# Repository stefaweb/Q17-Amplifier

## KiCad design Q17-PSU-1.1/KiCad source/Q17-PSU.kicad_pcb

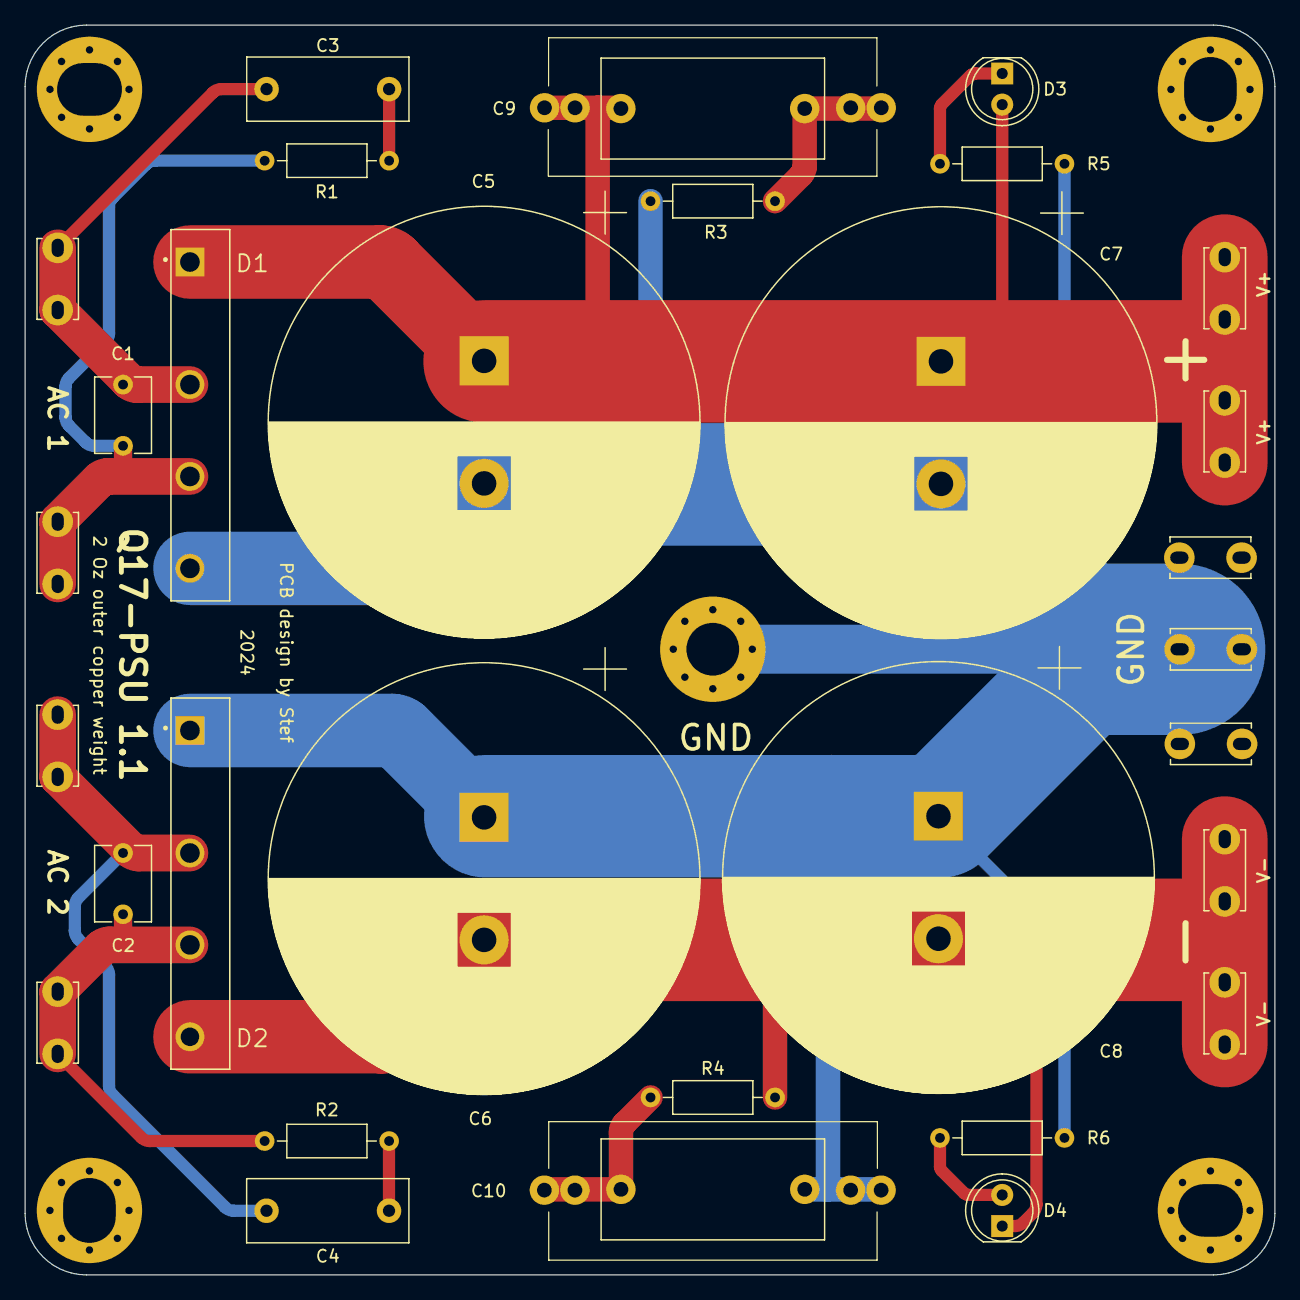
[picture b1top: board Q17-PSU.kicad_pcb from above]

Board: 2 copper layers, 102.0 x 102.0 mm, 31 parts (0 on the bottom side), 13 nets.

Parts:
C1, C2: 10nF; C_Disc_D6.0mm_W4.4mm_P5.00mm
C3, C4: 10nF; C_Rect_L13.0mm_W5.0mm_P10.00mm_FKS3_FKP3_MKS4
C5, C6, C7, C8: 10000uF 63v; CP_Radial_D35.0mm_P10.00mm_SnapIn
C9: 220nf; C_Rect_Q17_PSU_L26.50_H11.00_P20.50
C10: 220nF; C_Rect_Q17_PSU_L26.50_H11.00_P20.50
D1, D2: GBJ2510; DIOB_GBJ2510
D3, D4: LED; LED_D5.0mm
J1-1: AC1-1; Faston_Connector_63849-1_TEC
J1-2: AC1-2; Faston_Connector_63849-1_TEC
J1-3: AC2-1; Faston_Connector_63849-1_TEC
J1-4: AC2-2; Faston_Connector_63849-1_TEC
J2-1, J2-2: V+; Faston_Connector_63849-1_TEC
J2-3, J2-4, J2-5: GNDPWR; Faston_Connector_63849-1_TEC
J2-6, J2-7: V-; Faston_Connector_63849-1_TEC
R1, R2, R3, R4: 10R; R_Axial_DIN0207_L6.3mm_D2.5mm_P10.16mm_Horizontal
R5, R6: 10K; R_Axial_DIN0207_L6.3mm_D2.5mm_P10.16mm_Horizontal

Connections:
GNDPWR: C5.2, C6.1, C7.2, C8.1, C10.1, D1.4, D2.1, J2-3.1, J2-4.1, J2-5.1, R3.2, R5.2, R6.1
unnamed: C3.2, R1.1
unnamed: C4.2, R2.1
unnamed: C9.2, R3.1
unnamed: C10.2, R4.1
unnamed: C5.1, C7.1, C9.1, D1.1, D3.2 (A), J2-1.1, J2-2.1
unnamed: D3.1 (K), R5.1
unnamed: D4.2 (A), R6.2
unnamed: C6.2, C8.2, D2.4, D4.1 (K), J2-6.1, J2-7.1, R4.2
unnamed: C1.1, C3.1, D1.2, J1-1.1
unnamed: C1.2, D1.3, J1-2.1, R1.2
unnamed: C2.1, C4.1, D2.2, J1-3.1
unnamed: C2.2, D2.3, J1-4.1, R2.2

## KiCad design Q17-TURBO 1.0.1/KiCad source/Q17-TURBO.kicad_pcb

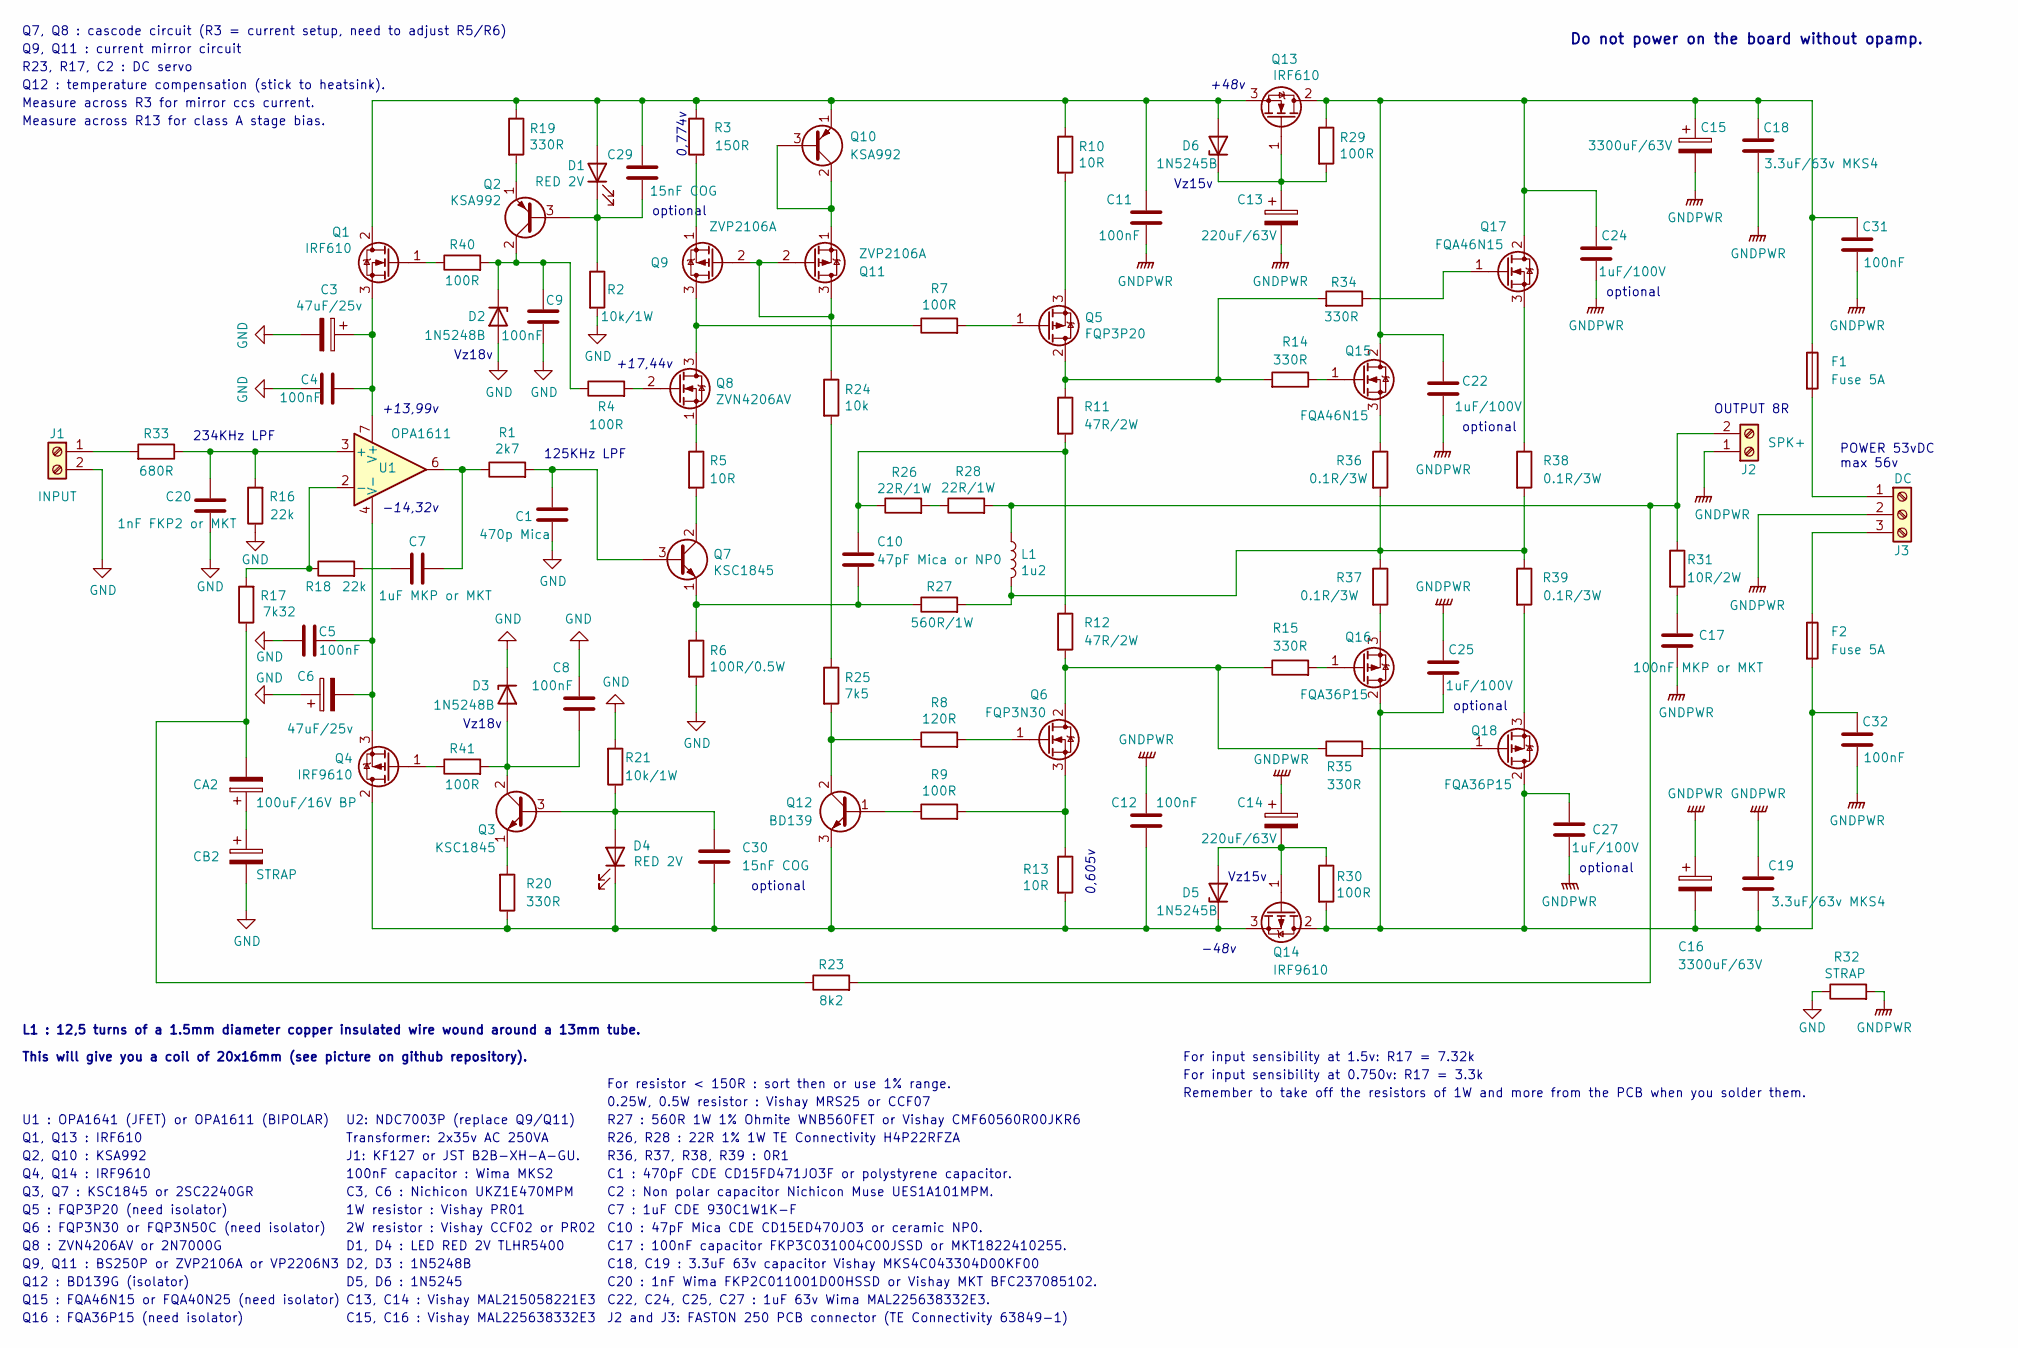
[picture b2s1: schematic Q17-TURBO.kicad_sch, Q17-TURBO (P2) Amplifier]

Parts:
C1: 470p Mica; C_Mica_v2_L11.4mm_W4.3mm_H9.1_P5.9mm_mix; Part# CD15FD471JO3F
C3, C6: 47uF/25v; CP_Radial_D10.0mm_P5.00mm; Part# Nichicon Muse UKZ1E470MPM
C4, C5, C8, C9, C11, C12, C31, C32: 100nF; C_Rect_L7.2mm_W2.5mm_P5.00mm_FKS2_FKP2_MKS2_MKP2; Part# MKS2D031001A00KSSD
C7: 1uF MKP or MKT; C_Rect_C7_Q17_Mini_L26.50_H11.00_P20.50_2; Part# CDE 930C1W1K-F
C10: 47pF Mica or NP0; C_Mica_v2_L11.4mm_W4.3mm_H9.1_P5.9mm_mix; Part# CD15ED470JO3
C13, C14: 220uF/63V; CP_Radial_D12.5mm_P5.00mm; Part# MAL215058221E3
C15, C16: 3300uF/63V; CP_Radial_D25.0mm_P10.00mm_SnapIn; Part# MAL225638332E3
C17: 100nF MKP or MKT; C_Rect_L18.0mm_W7.0mm_P15.00mm_C17; Part# FKP3D031004D00JF00
C18, C19: 3.3uF/63v MKS4; C_Rect_L18.0mm_W6.0mm_P15.00mm_FKS3_FKP3; Part# MKS4C043304D00KF00
C20: 1nF FKP2 or MKT; C_Mica_v2_L11.4mm_W4.3mm_H9.1_P5.9mm_mix; Part# FKP2D011001D00JSSD
C22, C24, C25, C27: 1uF/100V; C_Rect_L7.2mm_W7.2mm_P5.00mm_FKS2_FKP2_MKS2_MKP2; Part# MKS2D041001K00JSSD
C29, C30: 15nF COG; C_1206_3216Metric; Part# C3216NP01H153J060AA
CA2: 100uF/16V BP; CP_Radial_D10.0mm_P5.00mm; Part# UES1A101MPM
CB2: STRAP; CP_Radial_D10.0mm_P5.00mm; Part# STRAP
D1, D4: RED 2V; LED_D5.0mm; Part# TLHR5400
D2, D3: 1N5248B; D_DO-35_SOD27_P7.62mm_Horizontal; Part# 1N5248B
D5, D6: 1N5245B; D_DO-35_SOD27_P7.62mm_Horizontal; Part# 1N5245BTR
F1, F2: Fuse 5A; fuse_holder_CQ-2; Part# PCB fuse socket
J1: INPUT; Input_connector_mix_regular; Part# Terminal Block KF127 5mm 2P
J2: SPK+; AMASS_XT30U-F_1x02_P5.0mm_Vertical; Part# XT30 Male & Female Bullet Connector
J3: DC; TerminalBlock_Phoenix_PT-1,5-3-5.0-H_1x03_P5.00mm_Horizontal; Part# Terminal Block KF128 5mm 3P
L1: 1u2; L_Radial_D13mm_Q17_P2; Part# L1 : 12,5 turns of a 1.5mm diameter cop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
Q1, Q13: IRF610; TO-220-3_Vertical; Part# IRF610PBF
Q2, Q10: KSA992; TO-92_Inline_Wide; Part# KSA992FBTA
Q3, Q7: KSC1845; TO-92_Inline_Wide; Part# KSC1845FTA
Q4, Q14: IRF9610; TO-220-3_Vertical; Part# IRF9610PBF
Q5: FQP3P20; TO-220-3_Horizontal_TabDown_6mmHole; Part# FQP3P20
Q6: FQP3N30; TO-220-3_Horizontal_TabDown_6mmHole; Part# FQP3N30
Q8: ZVN4206AV; TO-92S_Wide; Part# ZVN4206AV
Q9, Q11: ZVP2106A; TO-92S_Wide; Part# ZVP2106A
Q12: BD139; BD139_Horizontal_TabDown; Part# BD139G
Q15, Q17: FQA46N15; TO-3PB-3_Horizontal_TabDown_6mmHole; Part# FQA46N15
Q16, Q18: FQA36P15; TO-3PB-3_Horizontal_TabDown_6mmHole; Part# FQA36P15
R1: 2k7; R_Axial_DIN0207_L6.3mm_D2.5mm_P10.16mm_Horizontal; Part# MRS25000C2701FCT00
R2, R21: 10k/1W; R_Axial_DIN0207_L6.3mm_D2.5mm_P10.16mm_Horizontal; Part# PR01000101002JR500
R3: 150R; R_Axial_DIN0207_L6.3mm_D2.5mm_P10.16mm_Horizontal; Part# MRS25000C1500FCT00
R4, R7, R9, R29, R30, R40, R41: 100R; R_Axial_DIN0207_L6.3mm_D2.5mm_P10.16mm_Horizontal; Part# MRS25000C1000FC100
R5, R10, R13: 10R; R_Axial_DIN0207_L6.3mm_D2.5mm_P10.16mm_Horizontal; Part# MRS25000C1009FCT00
R6: 100R/0.5W; R_Axial_DIN0207_L6.3mm_D2.5mm_P10.16mm_Horizontal; Part# MRS25000C1000FC100
R8: 120R; R_Axial_DIN0207_L6.3mm_D2.5mm_P10.16mm_Horizontal; Part# MRS25000C1200FCT
R11, R12: 47R/2W; R_Axial_DIN0411_L9.9mm_D3.6mm_P12.70mm_Horizontal; Part# CCF0247R0JKE36
R14, R15, R19, R20, R34, R35: 330R; R_Axial_DIN0207_L6.3mm_D2.5mm_P10.16mm_Horizontal; Part# MRS25000C3300FC1
R16, R18: 22k; R_Axial_DIN0207_L6.3mm_D2.5mm_P10.16mm_Horizontal; Part# MRS25000C2202FCT00
R17: 7k32; R_Axial_DIN0207_L6.3mm_D2.5mm_P10.16mm_Horizontal; Part# MF1/4CCT52R7321F
R23: 8k2; R_Axial_DIN0207_L6.3mm_D2.5mm_P10.16mm_Horizontal; Part# MRS25000C8201FCT
R24: 10k; R_Axial_DIN0207_L6.3mm_D2.5mm_P10.16mm_Horizontal; Part# MRS25000C1009FCT00
R25: 7k5; R_Axial_DIN0207_L6.3mm_D2.5mm_P10.16mm_Horizontal; Part# MRS25000C7501FCT00
R26, R28: 22R/1W; R_Axial_DIN0411_L9.9mm_D3.6mm_P12.70mm_Horizontal; Part# H4P22RFZA
R27: 560R/1W; R_Axial_DIN0411_L9.9mm_D3.6mm_P12.70mm_Horizontal; Part# WNB560FET
R31: 10R/2W; R_Axial_L12.0mm_D5.0mm_P15.24mm_Horizontal_Dale_1W; Part# PR02000201009JR500
R32: STRAP; R_Axial_DIN0207_L6.3mm_D2.5mm_P10.16mm_Horizontal; Part# STRAP
R33: 680R; R_Axial_DIN0207_L6.3mm_D2.5mm_P10.16mm_Horizontal; Part# MRS25000C6800FCT00
R36, R37: 0.1R/3W; R_Axial_DIN0614_L14.3mm_D5.7mm_P7.62mm_Vertical; Part# KOA MOSX3CT631RR10J
R38, R39: 0.1R/3W; R_Axial_DIN0614_L14.3mm_D5.7mm_P20.32mm_Horizontal; Part# KOA MOSX3CT631RR10J
U1: OPA1611; SOIC-8_3.9x4.9mm_P1.27mm; Part# OPA1611AID

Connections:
GND: C1.2, C3.2, C4.1, C5.1, C6.1, C8.1, C9.1, C20.1, CB2.2, D2.2 (A), D3.1 (K), J1.2, R2.2, R6.2, R16.1, R21.2, R32.1; also elsewhere on the board
GNDPWR: C11.1, C12.1, C13.2, C14.1, C15.2, C16.1, C17.2, C18.1, C19.2, C22.1, C24.1, C25.1, C27.1, C31.1, C32.1, J2.1, J3.2, R32.2
unnamed: C1.1, Q7.3 (B), R1.2
unnamed 3: C3.1, C4.2, Q1.3 (S), U1.7 (V+); also elsewhere on the board
unnamed 4: C5.2, C6.2, Q4.3 (S), U1.4 (V-); also elsewhere on the board
unnamed: C7.1, R18.2
unnamed 6: C7.2, R1.1, U1.6; also elsewhere on the board
unnamed: C8.2, D3.2 (A), Q3.2 (C), R41.2
unnamed: C9.2, D2.1 (K), Q2.2 (C), R4.1, R40.2
unnamed: C10.1, R11.2, R12.1, R26.1
unnamed: C10.2, Q7.1 (E), R6.1, R27.1
unnamed: C11.2, C29.1, D1.2 (A), D6.2 (A), Q1.2 (D), Q10.1 (E), Q13.3 (S), R3.1, R10.1, R19.1
unnamed: C12.2, C30.2, D4.1 (K), D5.1 (K), Q4.2 (D), Q12.3 (E), Q14.3 (S), R13.2, R20.1
unnamed: C13.1, D6.1 (K), Q13.1 (G), R29.2
unnamed: C14.2, D5.2 (A), Q14.1 (G), R30.1
unnamed: C15.1, C18.2, C22.2, C24.2, C31.2, F1.1, Q13.2 (D), Q15.2 (D), Q17.2 (D), R29.1
unnamed: C16.2, C19.1, C25.2, C27.2, C32.2, F2.2, Q14.2 (D), Q16.2 (D), Q18.2 (D), R30.2
unnamed: C17.1, R31.2
unnamed 18: C20.2, R16.2, R33.1, U1.3 (+); also elsewhere on the board
unnamed: C29.2, D1.1 (K), Q2.3 (B), R2.1
unnamed: C30.1, D4.2 (A), Q3.3 (B), R21.1
unnamed: CA2.1, CB2.1
unnamed: CA2.2, R17.1, R23.1
unnamed: F1.2, J3.1
unnamed: F2.1, J3.3
unnamed: J1.1, R33.2
unnamed: J2.2, L1.1, R23.2, R28.2, R31.1
unnamed: L1.2, R27.2, R36.2, R37.1, R38.2, R39.1
unnamed: Q1.1 (G), R40.1
unnamed: Q2.1 (E), R19.2
unnamed: Q3.1 (E), R20.2
unnamed: Q4.1 (G), R41.1
unnamed: Q5.1 (G), R7.2
unnamed: Q5.2 (D), R11.1, R14.2, R34.2
unnamed: Q5.3 (S), R10.2
unnamed: Q6.1 (G), R8.2
unnamed: Q6.2 (D), R12.2, R15.1, R35.1
unnamed: Q6.3 (S), R9.2, R13.1
unnamed: Q7.2 (C), R5.2
unnamed: Q8.1 (S), R5.1
unnamed: Q8.2 (G), R4.2
unnamed 41: Q8.3 (D), Q9.3 (D), R7.1; also elsewhere on the board
unnamed 42: Q9.1 (S), R3.2; also elsewhere on the board
unnamed 43: Q10.2 (C), Q10.3 (B), Q11.1 (S); also elsewhere on the board
unnamed 44: Q9.2 (G), Q11.2 (G), Q11.3 (D), R24.1; also elsewhere on the board
unnamed: Q12.1 (B), R9.1
unnamed: Q12.2 (C), R8.1, R25.2
unnamed: Q15.1 (G), R14.1
unnamed: Q15.3 (S), R36.1
unnamed: Q16.1 (G), R15.2
unnamed: Q16.3 (S), R37.2
unnamed: Q17.1 (G), R34.1
unnamed: Q17.3 (S), R38.1
unnamed: Q18.1 (G), R35.2
unnamed: Q18.3 (S), R39.2
unnamed 55: R17.2, R18.1, U1.2 (-); also elsewhere on the board
unnamed: R24.2, R25.1
unnamed: R26.2, R28.1

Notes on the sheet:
D1, D4 : LED RED 2V TLHR5400
Do not power on the board without opamp.
C10 : 47pF Mica CDE CD15ED470JO3 or ceramic NP0.
C15, C16 : Vishay MAL225638332E3
+13,99v
Vz15v
+48v
R27 : 560R 1W 1% Ohmite WNB560FET or Vishay CMF60560R00JKR6
Q12 : BD139G (isolator)
Q4, Q14 : IRF9610
C20 : 1nF Wima FKP2C011001D00HSSD or Vishay MKT BFC237085102.
D5, D6 : 1N5245
U1 : OPA1641 (JFET) or OPA1611 (BIPOLAR)
This will give you a coil of 20x16mm (see picture on github repository).
Q12 : temperature compensation (stick to heatsink).
Vz18v
C13, C14 : Vishay MAL215058221E3
C18, C19 : 3.3uF 63v capacitor Vishay MKS4C043304D00KF00
Q9, Q11 : BS250P or ZVP2106A or VP2206N3
Transformer: 2x35v AC 250VA
C1 : 470pF CDE CD15FD471JO3F or polystyrene capacitor.
J2 and J3: FASTON 250 PCB connector (TE Connectivity 63849-1)
optional
Q15 : FQA46N15 or FQA40N25 (need isolator)
0,774v
C17 : 100nF capacitor FKP3C031004C00JSSD or MKT1822410255.
R23, R17, C2 : DC servo
234KHz LPF
Q9, Q11 : current mirror circuit
Q1, Q13 : IRF610
OUTPUT 8R
Q3, Q7 : KSC1845 or 2SC2240GR
Q5 : FQP3P20 (need isolator)
L1 : 12,5 turns of a 1.5mm diameter copper insulated wire wound around a 13mm tube.
C22, C24, C25, C27 : 1uF 63v Wima MAL225638332E3.
Q7, Q8 : cascode circuit (R3 = current setup, need to adjust R5/R6)
For input sensibility at 0.750v: R17 = 3.3k
C3, C6 : Nichicon UKZ1E470MPM
1W resistor : Vishay PR01
C7 : 1uF CDE 930C1W1K-F

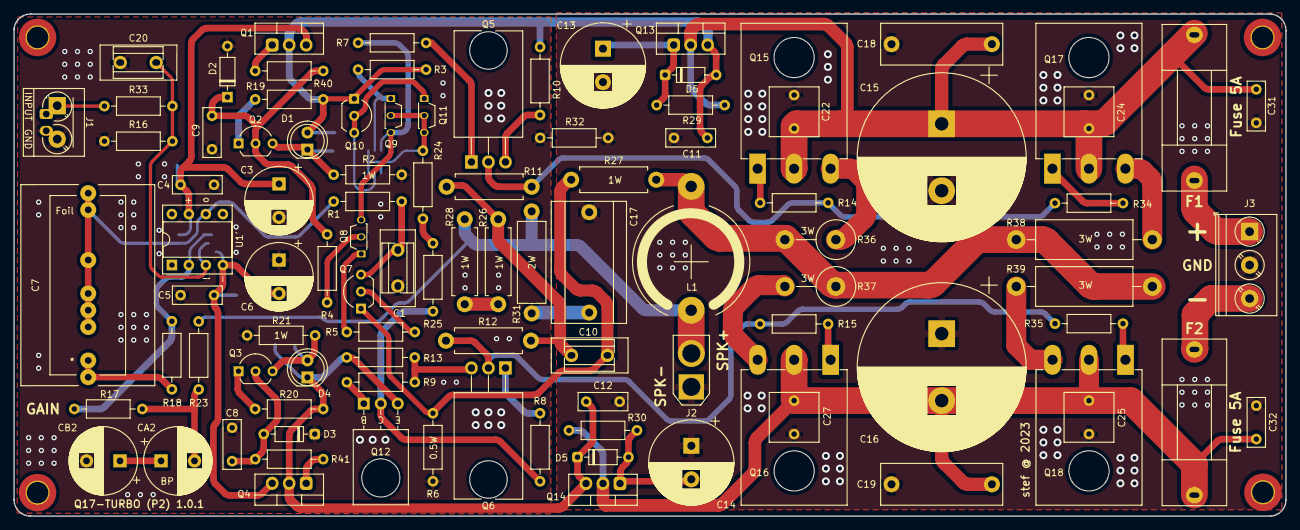
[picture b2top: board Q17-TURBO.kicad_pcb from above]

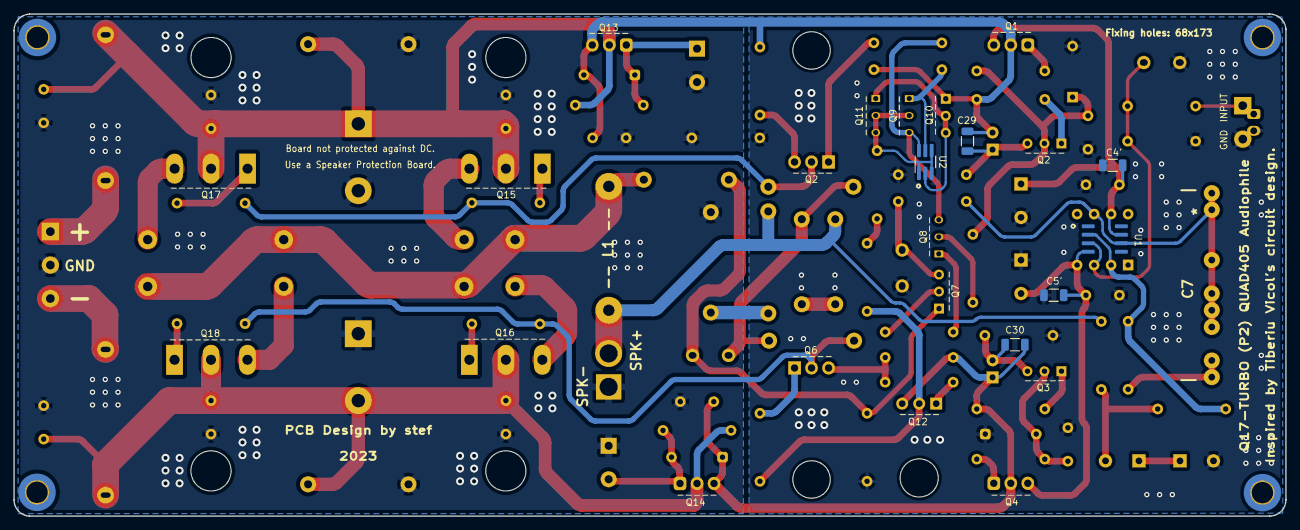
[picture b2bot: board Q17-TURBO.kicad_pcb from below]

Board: 2 copper layers, 190.0 x 75.0 mm, 108 parts (6 on the bottom side), 58 nets.

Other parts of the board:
C4': 100nF; C_1206_3216Metric
C5': 15nF COG; C_1206_3216Metric
H1, H1#2, H1#3, H1#4: MountingHole; MountingHole_3.2mm_M3_DIN965_Pad_TopBottom
U1': OPA1641; DIP-8_W7.62mm_Socket
U2: NDC7003P; TSOT-23-6_HandSoldering

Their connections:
GND: C4'.1, C5'.1; also elsewhere on the board
unnamed 3: C4'.2, U1'.7 (V+); also elsewhere on the board
unnamed 4: C5'.2, U1'.4 (V-); also elsewhere on the board
unnamed 6: U1'.6; also elsewhere on the board
unnamed 18: U1'.3 (+); also elsewhere on the board
unnamed 41: U2.6; also elsewhere on the board
unnamed 42: U2.5; also elsewhere on the board
unnamed 43: U2.2; also elsewhere on the board
unnamed 44: U2.1, U2.3, U2.4; also elsewhere on the board
unnamed 55: U1'.2 (-); also elsewhere on the board

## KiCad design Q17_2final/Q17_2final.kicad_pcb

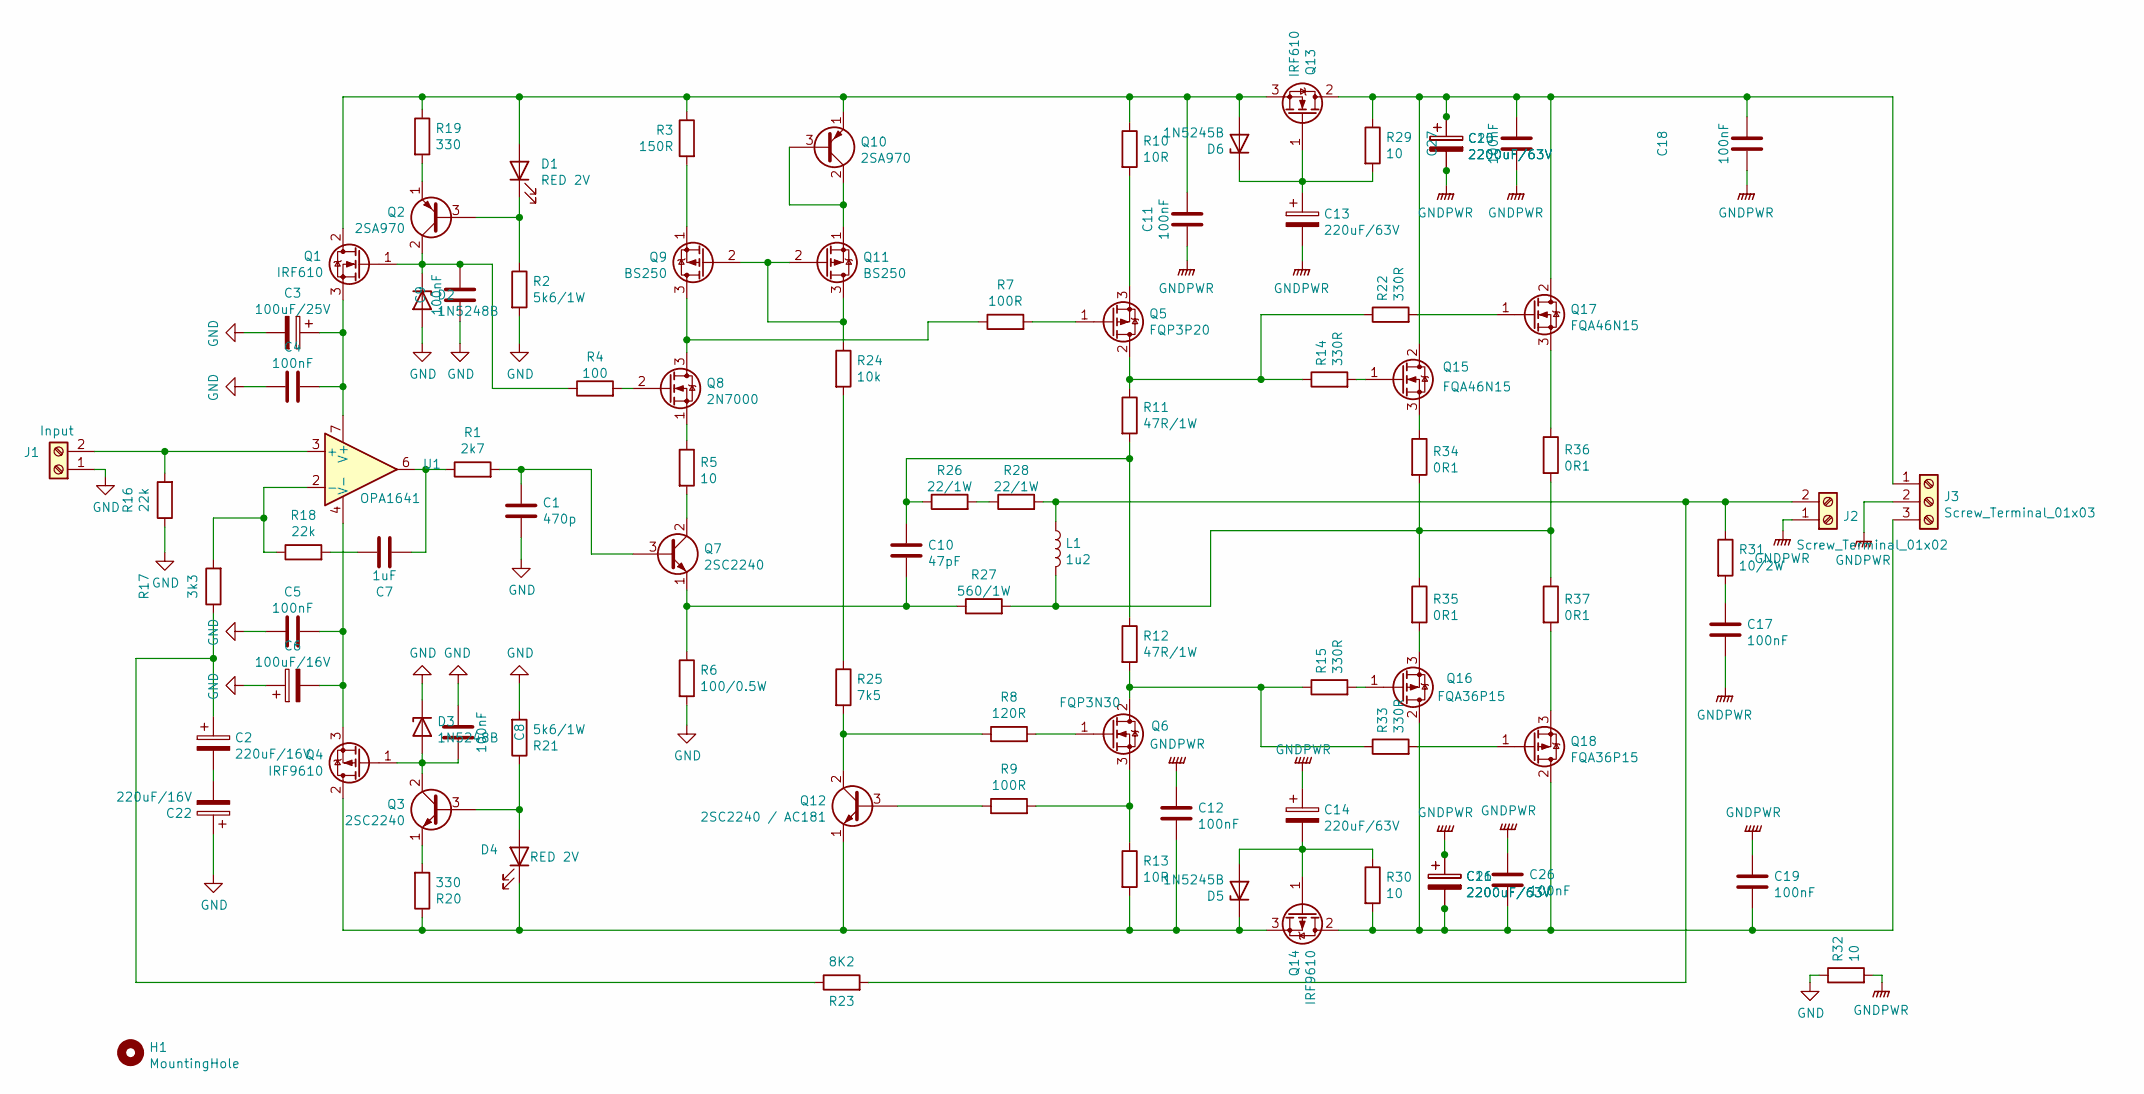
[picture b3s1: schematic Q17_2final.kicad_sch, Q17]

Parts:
C1: 470p; C_Disc_D11.0mm_W5.0mm_P7.50mm
C2, C22: 220uF/16V; C_Radial_D10.0mm_H12.5mm_P5.00mm
C3: 100uF/25V; C_Radial_D10.0mm_H12.5mm_P5.00mm
C4, C5, C8, C9, C11, C12, C18, C19, C26, C27: 100nF; C_Disc_D7.5mm_W2.5mm_P5.00mm
C6: 100uF/16V; C_Radial_D10.0mm_H12.5mm_P5.00mm
C7: 1uF; CP_Axial_L26.5mm_D20.0mm_P33.00mm_Horizontal
C10: 47pF; C_Disc_D11.0mm_W5.0mm_P7.50mm
C13, C14: 220uF/63V; CP_Radial_D10.0mm_P5.00mm_P7.50mm
C15, C16: 2200uF/63V; CP_Radial_D18.0mm_P7.50mm
C17: 100nF; C_Rect_L18.0mm_W11.0mm_P15.00mm_FKS3_FKP3
C20, C21: 2200uF/63V; CP_Radial_D22.0mm_P10.00mm_SnapIn
D1, D4: RED 2V; LED_D5.0mm_Clear
D2, D3: 1N5248B; D_DO-35_SOD27_P7.62mm_Horizontal
D5, D6: 1N5245B; D_DO-35_SOD27_P7.62mm_Horizontal
H1: MountingHole; MountingHole_3.2mm_M3_Pad_Via
J1: Input; Stocko_MKS_1651-6-0-202_1x2_P2.50mm_Vertical
J2: Screw_Terminal_01x02; AMASS_XT30U-F_1x02_P5.0mm_Vertical
J3: Screw_Terminal_01x03; TerminalBlock_Altech_AK300-3_P5.00mm
L1: 1u2; L_new
Q1, Q13: IRF610; TO-220-3_Vertical
Q2, Q10: 2SA970; TO-92
Q3, Q7: 2SC2240; TO-92
Q4, Q14: IRF9610; TO-220-3_Vertical
Q5: FQP3P20; TO-220-3_Vertical
Q6: FQP3N30; TO-220-3_Vertical
Q8: 2N7000; TO-92_Inline
Q9, Q11: BS250; TO-92L_Inline
Q12: 2SC2240 / AC181; TO-92
Q15, Q17: FQA46N15; TO-3P-3_Horizontal_TabDown
Q16, Q18: FQA36P15; TO-3P-3_Horizontal_TabDown
R1: 2k7; R_Axial_DIN0207_L6.3mm_D2.5mm_P10.16mm_Horizontal
R2, R21: 5k6/1W; R_Axial_DIN0207_L6.3mm_D2.5mm_P10.16mm_Horizontal
R3: 150R; R_Axial_DIN0207_L6.3mm_D2.5mm_P10.16mm_Horizontal
R4: 100; R_Axial_DIN0207_L6.3mm_D2.5mm_P10.16mm_Horizontal
R5, R29, R30, R32: 10; R_Axial_DIN0207_L6.3mm_D2.5mm_P10.16mm_Horizontal
R6: 100/0.5W; R_Axial_DIN0207_L6.3mm_D2.5mm_P10.16mm_Horizontal
R7, R9: 100R; R_Axial_DIN0207_L6.3mm_D2.5mm_P10.16mm_Horizontal
R8: 120R; R_Axial_DIN0207_L6.3mm_D2.5mm_P10.16mm_Horizontal
R10, R13: 10R; R_Axial_DIN0207_L6.3mm_D2.5mm_P10.16mm_Horizontal
R11, R12: 47R/1W; R_Axial_DIN0411_L9.9mm_D3.6mm_P12.70mm_Horizontal
R14, R15, R22, R33: 330R; R_Axial_DIN0207_L6.3mm_D2.5mm_P10.16mm_Horizontal
R16, R18: 22k; R_Axial_DIN0207_L6.3mm_D2.5mm_P10.16mm_Horizontal
R17: 3k3; R_Axial_DIN0207_L6.3mm_D2.5mm_P10.16mm_Horizontal
R19, R20: 330; R_Axial_DIN0207_L6.3mm_D2.5mm_P10.16mm_Horizontal
R23: 8K2; R_Axial_DIN0207_L6.3mm_D2.5mm_P10.16mm_Horizontal
R24: 10k; R_Axial_DIN0207_L6.3mm_D2.5mm_P10.16mm_Horizontal
R25: 7k5; R_Axial_DIN0207_L6.3mm_D2.5mm_P10.16mm_Horizontal
R26, R28: 22/1W; R_Axial_DIN0207_L6.3mm_D2.5mm_P10.16mm_Horizontal
R27: 560/1W; R_Axial_DIN0207_L6.3mm_D2.5mm_P10.16mm_Horizontal
R31: 10/2W; R_Axial_DIN0309_L9.0mm_D3.2mm_P12.70mm_Horizontal
R34, R35, R36, R37: 0R1; R_Axial_DIN0414_L11.9mm_D4.5mm_P5.08mm_Vertical
U1: OPA1641; SOIC-8_3.9x4.9mm_P1.27mm

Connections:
GND: C1.2, C3.2, C4.1, C5.1, C6.1, C8.1, C9.1, C22.1, D2.2 (A), D3.1 (K), J1.1, R2.2, R6.2, R16.1, R21.2, R32.1
GNDPWR: C11.1, C12.1, C13.2, C14.1, C15.2, C16.1, C17.2, C18.1, C19.2, C20.2, C21.1, C26.2, C27.1, J2.1, J3.2, R32.2
unnamed: C1.1, Q7.3 (B), R1.2
unnamed: C2.1, R17.1, R23.1
unnamed: C2.2, C22.2
unnamed: C3.1, C4.2, Q1.3 (S), U1.7 (V+)
unnamed: C5.2, C6.2, Q4.3 (S), U1.4 (V-)
unnamed: C7.1, R1.1, U1.6
unnamed: C7.2, R18.2
unnamed: C8.2, D3.2 (A), Q3.2 (C), Q4.1 (G)
unnamed: C9.2, D2.1 (K), Q1.1 (G), Q2.2 (C), R4.1
unnamed: C10.1, R11.2, R12.1, R26.1
unnamed: C10.2, Q7.1 (E), R6.1, R27.1
unnamed: C11.2, D1.2 (A), D6.2 (A), Q1.2 (D), Q10.1 (E), Q13.3 (S), R3.1, R10.1, R19.1
unnamed: C12.2, D4.1 (K), D5.1 (K), Q4.2 (D), Q12.1 (E), Q14.3 (S), R13.2, R20.1
unnamed: C13.1, D6.1 (K), Q13.1 (G), R29.2
unnamed: C14.2, D5.2 (A), Q14.1 (G), R30.1
unnamed: C15.1, C18.2, C20.1, C27.2, J3.1, Q13.2 (D), Q15.2 (D), Q17.2 (D), R29.1
unnamed: C16.2, C19.1, C21.2, C26.1, J3.3, Q14.2 (D), Q16.2 (D), Q18.2 (D), R30.2
unnamed: C17.1, R31.2
unnamed: D1.1 (K), Q2.3 (B), R2.1
unnamed: D4.2 (A), Q3.3 (B), R21.1
unnamed: J1.2, R16.2, U1.3 (+)
unnamed: J2.2, L1.1, R23.2, R28.2, R31.1
unnamed: L1.2, R27.2, R34.2, R35.1, R36.2, R37.1
unnamed: Q2.1 (E), R19.2
unnamed: Q3.1 (E), R20.2
unnamed: Q5.1 (G), R7.2
unnamed: Q5.2 (D), R11.1, R14.1, R22.1
unnamed: Q5.3 (S), R10.2
unnamed: Q6.1 (G), R8.2
unnamed: Q6.2 (D), R12.2, R15.1, R33.1
unnamed: Q6.3 (S), R9.2, R13.1
unnamed: Q7.2 (C), R5.2
unnamed: Q8.1 (S), R5.1
unnamed: Q8.2 (G), R4.2
unnamed: Q8.3 (D), Q9.3 (D), R7.1
unnamed: Q9.1 (S), R3.2
unnamed: Q10.2 (C), Q10.3 (B), Q11.1 (S)
unnamed: Q9.2 (G), Q11.2 (G), Q11.3 (D), R24.1
unnamed: Q12.2 (C), R8.1, R25.2
unnamed: Q12.3 (B), R9.1
unnamed: Q15.1 (G), R14.2
unnamed: Q15.3 (S), R34.1
unnamed: Q16.1 (G), R15.2
unnamed: Q16.3 (S), R35.2
unnamed: Q17.1 (G), R22.2
unnamed: Q17.3 (S), R36.1
unnamed: Q18.1 (G), R33.2
unnamed: Q18.3 (S), R37.2
unnamed: R17.2, R18.1, U1.2 (-)
unnamed: R24.2, R25.1
unnamed: R26.2, R28.1

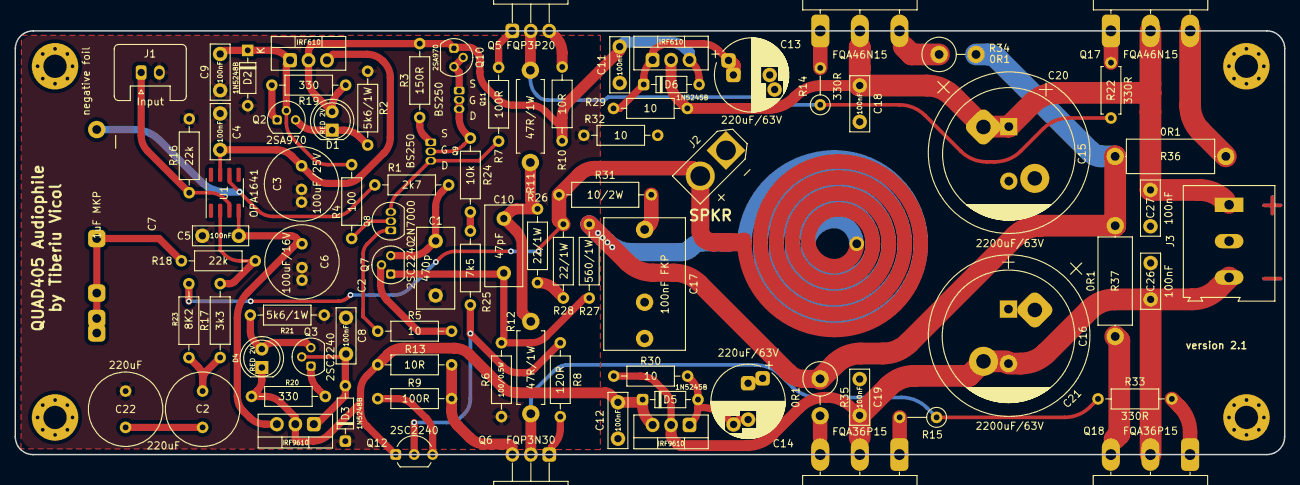
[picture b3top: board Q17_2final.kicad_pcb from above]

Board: 2 copper layers, 174.7 x 58.3 mm, 94 parts (0 on the bottom side), 53 nets.

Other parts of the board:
H1#2, H1#3, H1#4: MountingHole; MountingHole_3.2mm_M3_Pad_Via
